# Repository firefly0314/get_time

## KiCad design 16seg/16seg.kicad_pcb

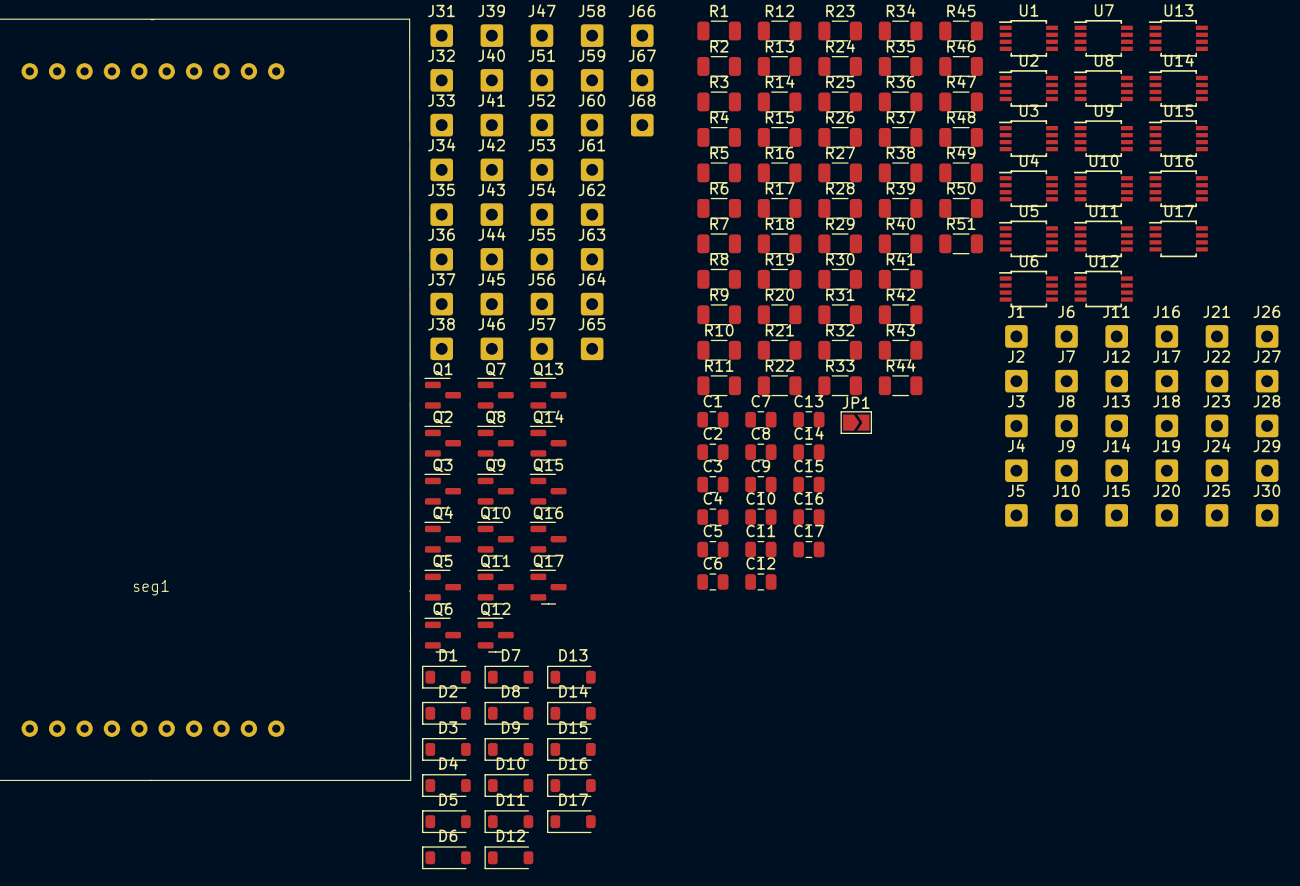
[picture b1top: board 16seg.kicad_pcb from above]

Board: 2 copper layers, 186 parts (0 on the bottom side), 115 nets, no tracks yet.

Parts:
C1, C2, C3, C4, C5, C6, C7, C8, C9, C10, C11, C12, C13, C14, C15, C16, C17: C; C_0805_2012Metric
D1, D2, D3, D4, D5, D6, D7, D8, D9, D10, D11, D12, D13, D14, D15, D16, D17: NSI45015WT1G; D_SOD-123
J1, J2, J3, J4, J5, J6, J7, J8, J9, J10, J11, J12: Conn_01x01; SolderWire-0.5sqmm_1x01_D0.9mm_OD2.1mm
J13, J31: A1; SolderWire-0.5sqmm_1x01_D0.9mm_OD2.1mm
J14, J32: A2; SolderWire-0.5sqmm_1x01_D0.9mm_OD2.1mm
J15, J33: B; SolderWire-0.5sqmm_1x01_D0.9mm_OD2.1mm
J16, J34: C; SolderWire-0.5sqmm_1x01_D0.9mm_OD2.1mm
J17, J35: D1; SolderWire-0.5sqmm_1x01_D0.9mm_OD2.1mm
J18, J36: D2; SolderWire-0.5sqmm_1x01_D0.9mm_OD2.1mm
J19, J37: E; SolderWire-0.5sqmm_1x01_D0.9mm_OD2.1mm
J20, J38: F; SolderWire-0.5sqmm_1x01_D0.9mm_OD2.1mm
J21, J39: G1; SolderWire-0.5sqmm_1x01_D0.9mm_OD2.1mm
J22, J40: G2; SolderWire-0.5sqmm_1x01_D0.9mm_OD2.1mm
J23, J41: H; SolderWire-0.5sqmm_1x01_D0.9mm_OD2.1mm
J24, J42: I; SolderWire-0.5sqmm_1x01_D0.9mm_OD2.1mm
J25, J43: J; SolderWire-0.5sqmm_1x01_D0.9mm_OD2.1mm
J26, J44: K; SolderWire-0.5sqmm_1x01_D0.9mm_OD2.1mm
J27, J45: L; SolderWire-0.5sqmm_1x01_D0.9mm_OD2.1mm
J28, J46: M; SolderWire-0.5sqmm_1x01_D0.9mm_OD2.1mm
J29, J47, J54: DP; SolderWire-0.5sqmm_1x01_D0.9mm_OD2.1mm
J30, J55, J56, J65: OF; SolderWire-0.5sqmm_1x01_D0.9mm_OD2.1mm
J51, J52, J63: VCC; SolderWire-0.5sqmm_1x01_D0.9mm_OD2.1mm
J53, J64: deta; SolderWire-0.5sqmm_1x01_D0.9mm_OD2.1mm
J57, J58, J66: CLR; SolderWire-0.5sqmm_1x01_D0.9mm_OD2.1mm
J59, J60, J67: CK; SolderWire-0.5sqmm_1x01_D0.9mm_OD2.1mm
J61, J62, J68: GND; SolderWire-0.5sqmm_1x01_D0.9mm_OD2.1mm
JP1: Jumper_2_Bridged; SolderJumper-2_P1.3mm_Open_TrianglePad1.0x1.5mm
Q1, Q2, Q3, Q4, Q5, Q6, Q7, Q8, Q9, Q10, Q11, Q12, Q13, Q14, Q15, Q16, Q17: BSS138; SOT-23
R1, R2, R3, R4, R5, R6, R7, R8, R9, R10, R11, R12, R13, R14, R15, R16, R17, R18, R19, R20, R21, R22, R23, R24, R25, R26, R27, R28, R29, R30, R31, R32, R33, R34, R35, R36, R37, R38, R39, R40, R41, R42, R43, R44, R45, R46, R47, R48, R49, R50, R51: 10k; R_1206_3216Metric
U1, U2, U3, U4, U5, U6, U7, U8, U9, U10, U11, U12, U13, U14, U15, U16, U17: TSSOP-8_3x3mm_P0.65mm
seg1: 16seg

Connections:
+5F: J51.1, J52.1, J63.1, seg1.1 (Anode), seg1.11 (Anode)
+5V: C1.1, C2.1, C3.1, C4.1, C5.1, C6.1, C7.1, C8.1, C9.1, C10.1, C11.1, C12.1, C13.1, C14.1, C15.1, C16.1, C17.1, J1.1, J7.1, U1.8 (vcc), U2.8 (vcc), U3.8 (vcc), U4.8 (vcc), U5.8 (vcc), U6.8 (vcc), U7.8 (vcc), U8.8 (vcc), U9.8 (vcc), U10.8 (vcc), U11.8 (vcc), U12.8 (vcc), U13.8 (vcc), U14.8 (vcc), U15.8 (vcc), U16.8 (vcc), U17.8 (vcc)
CK: J5.1, J11.1, U1.1 (CK), U2.1 (CK), U3.1 (CK), U4.1 (CK), U5.1 (CK), U6.1 (CK), U7.1 (CK), U8.1 (CK), U9.1 (CK), U10.1 (CK), U11.1 (CK), U12.1 (CK), U13.1 (CK), U14.1 (CK), U15.1 (CK), U16.1 (CK), U17.1 (CK)
CK_LED: J59.1, J60.1, J67.1
CLR: J4.1, J10.1, U1.6 (CLR), U2.6 (CLR), U3.6 (CLR), U4.6 (CLR), U5.6 (CLR), U6.6 (CLR), U7.6 (CLR), U8.6 (CLR), U9.6 (CLR), U10.6 (CLR), U11.6 (CLR), U12.6 (CLR), U13.6 (CLR), U14.6 (CLR), U15.6 (CLR), U16.6 (CLR), U17.6 (CLR)
CLR_LED: J57.1, J58.1, J66.1
GND: C1.2, C2.2, C3.2, C4.2, C5.2, C6.2, C7.2, C8.2, C9.2, C10.2, C11.2, C12.2, C13.2, C14.2, C15.2, C16.2, C17.2, J6.1, J12.1, R1.1, R2.1, R3.1, R4.1, R5.1, R6.1, R7.1, R8.1, R9.1, R10.1, R11.1, R12.1, R13.1, R14.1, R15.1, R16.1, R17.1, R18.1, R19.1, R20.1, R21.1, R22.1, R23.1, R24.1, R25.1, R26.1, R27.1, R28.1, R29.1, R30.1, R31.1, R32.1, R33.1, R34.1, R35.1, R36.1, R37.1, R38.1, R39.1, R40.1, R41.1, R42.1, R43.1, R44.1, R45.1, R46.1, R47.1, R48.1, R49.1, R50.1, R51.1, U1.4 (gnd), U2.4 (gnd), U3.4 (gnd), U4.4 (gnd), U5.4 (gnd), U6.4 (gnd), U7.4 (gnd), U8.4 (gnd), U9.4 (gnd), U10.4 (gnd), U11.4 (gnd), U12.4 (gnd), U13.4 (gnd), U14.4 (gnd), U15.4 (gnd), U16.4 (gnd), U17.4 (gnd)
GND2: J61.1, J62.1, J68.1, Q1.2 (S), Q2.2 (S), Q3.2 (S), Q4.2 (S), Q5.2 (S), Q6.2 (S), Q7.2 (S), Q8.2 (S), Q9.2 (S), Q10.2 (S), Q11.2 (S), Q12.2 (S), Q13.2 (S), Q14.2 (S), Q15.2 (S), Q16.2 (S), Q17.2 (S)
unnamed: J13.1, R35.2, U1.5 (Q), U2.2 (D)
unnamed: J14.1, R36.2, U2.5 (Q), U3.2 (D)
unnamed: J15.1, R37.2, U3.5 (Q), U4.2 (D)
unnamed: J16.1, R38.2, U4.5 (Q), U5.2 (D)
unnamed: J17.1, R39.2, U5.5 (Q), U6.2 (D)
unnamed: J18.1, R40.2, U6.5 (Q), U7.2 (D)
unnamed: J19.1, R41.2, U7.5 (Q), U8.2 (D)
unnamed: J20.1, R42.2, U8.5 (Q), U9.2 (D)
unnamed: J22.1, R44.2, U10.5 (Q), U11.2 (D)
unnamed: J23.1, R45.2, U11.5 (Q), U12.2 (D)
unnamed: J24.1, R46.2, U12.5 (Q), U13.2 (D)
unnamed: J25.1, R47.2, U13.5 (Q), U14.2 (D)
unnamed: J26.1, R48.2, U14.5 (Q), U15.2 (D)
unnamed: J27.1, R49.2, U15.5 (Q), U16.2 (D)
unnamed: J28.1, R50.2, U16.5 (Q), U17.2 (D)
unnamed: J29.1, JP1.1 (A), R51.2, U17.5 (Q)
unnamed: J30.1, JP1.2 (B)
unnamed: J31.1, Q1.1 (G)
unnamed: J32.1, Q2.1 (G)
unnamed: J33.1, Q3.1 (G)
unnamed: J34.1, Q4.1 (G)
unnamed: J35.1, Q5.1 (G)
unnamed: J36.1, Q6.1 (G)
unnamed: J37.1, Q7.1 (G)
unnamed: J38.1, Q8.1 (G)
unnamed: J39.1, Q9.1 (G)
unnamed: J40.1, Q10.1 (G)
unnamed: J41.1, Q11.1 (G)
unnamed: J42.1, Q12.1 (G)
unnamed: J43.1, Q13.1 (G)
unnamed: J44.1, Q14.1 (G)
unnamed: J45.1, Q15.1 (G)
unnamed: J46.1, Q16.1 (G)
unnamed: J47.1, Q17.1 (G)
unnamed: D1.1, Q1.3 (D)
unnamed: D2.1, Q2.3 (D)
unnamed: D3.1, Q3.3 (D)
unnamed: D4.1, Q4.3 (D)
unnamed: D5.1, Q5.3 (D)
unnamed: D6.1, Q6.3 (D)
unnamed: D7.1, Q7.3 (D)
unnamed: D8.1, Q8.3 (D)
unnamed: D9.1, Q9.3 (D)
unnamed: D10.1, Q10.3 (D)
unnamed: D11.1, Q11.3 (D)
unnamed: D12.1, Q12.3 (D)
unnamed: D13.1, Q13.3 (D)
unnamed: D14.1, Q14.3 (D)
unnamed: D15.1, Q15.3 (D)
unnamed: D16.1, Q16.3 (D)
unnamed: D17.1, Q17.3 (D)
unnamed: R1.2, U1.7 (PR)
unnamed: R10.2, U1.3 (Q-)
unnamed: R2.2, U2.7 (PR)
unnamed: R11.2, U2.3 (Q-)
unnamed: R3.2, U3.7 (PR)
unnamed: R12.2, U3.3 (Q-)
unnamed: R4.2, U4.7 (PR)
unnamed: R13.2, U4.3 (Q-)
unnamed: R5.2, U5.7 (PR)
unnamed: R14.2, U5.3 (Q-)
unnamed: R6.2, U6.7 (PR)
unnamed: R15.2, U6.3 (Q-)
unnamed: R7.2, U7.7 (PR)
unnamed: R16.2, U7.3 (Q-)
unnamed: R8.2, U8.7 (PR)
unnamed: R17.2, U8.3 (Q-)
unnamed: R9.2, U9.7 (PR)
unnamed: R18.2, U9.3 (Q-)
unnamed: R19.2, U10.7 (PR)
unnamed: R27.2, U10.3 (Q-)
unnamed: R20.2, U11.7 (PR)
unnamed: R28.2, U11.3 (Q-)
unnamed: R21.2, U12.7 (PR)
unnamed: R29.2, U12.3 (Q-)
unnamed: R22.2, U13.7 (PR)
unnamed: R30.2, U13.3 (Q-)
unnamed: R23.2, U14.7 (PR)
unnamed: R31.2, U14.3 (Q-)
unnamed: R24.2, U15.7 (PR)
unnamed: R32.2, U15.3 (Q-)
unnamed: R25.2, U16.7 (PR)
unnamed: R33.2, U16.3 (Q-)
unnamed: R26.2, U17.7 (PR)
unnamed: R34.2, U17.3 (Q-)
unnamed: D1.2, seg1.17 (A1)
unnamed: D2.2, seg1.14 (A2)
unnamed: D3.2, seg1.13 (B)
unnamed: D4.2, seg1.9 (C)
unnamed: D5.2, seg1.4 (D1)
unnamed: D6.2, seg1.7 (D2)
unnamed: D17.2, seg1.10 (DP)
unnamed: D7.2, seg1.3 (E)
unnamed: D8.2, seg1.19 (F)
unnamed: D9.2, seg1.2 (G1)
unnamed: D10.2, seg1.12 (G2)
unnamed: D11.2, seg1.18 (H)
unnamed: D12.2, seg1.16 (I)
unnamed: D13.2, seg1.15 (J)
unnamed: D14.2, seg1.8 (K)
unnamed: D15.2, seg1.6 (L)
unnamed: D16.2, seg1.5 (M)
OF: J3.1, J9.1
OF_LED: J55.1, J56.1, J65.1
Q_D: J21.1, R43.2, U9.5 (Q), U10.2 (D)
deta: J2.1, U1.2 (D)
deta_LED: J53.1, J64.1

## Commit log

2023-04-29 0.22
2023-04-29 0.3a
2023-04-29 0.35
2023-05-04 16seg
2023-05-04 0.68
2023-05-05 0.61
2023-05-05 pcbs
2023-05-06 -logisim-win-2.7.1.exe
2023-05-06 0.62
2023-05-06 -__pycache__
2023-05-06 libf
2023-05-06 set lib
2023-05-07 0.65
2023-05-15 15:23
2023-05-16 toml add
2023-05-17 2023-05-17
2023-05-17 17:23
2023-05-26 2023/05/26
2023-05-27 2023/05/27
